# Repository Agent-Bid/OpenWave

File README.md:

# OpenWave

This is an attempt to make an open-source, modern(ish) digital audio player using commonly available parts today with a simple menu-based operating system shell.

## Firmware Build Instructions

This project uses [PlatformIO](https://platformio.org/) for firmware development. The project is being developed with an ESP32 Devkit V1 (esp32dev).

### Prerequisites
* [PlatformIO CLI](https://docs.platformio.org/en/latest/core/index.html)
* Or [PlatformIO IDE - VSCode](https://docs.platformio.org/en/latest/integration/ide/vscode.html)

### Building
1. Navigate to the firmware directory: `cd Firmware/OpenWave_Firmware`
2. Resolve dependencies and build project: `pio run`

### Uploading
1. Connect the ESP32 board via USB and run: `pio run -t upload`
2. To monitor serial from the board: `pio device monitor`

## Hardware Used
All software tested on:
1. ESP32 Devkit V1
2. Adafruit VS1053b Breakout
3. SSD1306 OLED

Custom 4 layer PCB designed in KiCad

## Assembled Board

## Licensing

This is an open-source hardware project. To ensure all aspects of the design are properly protected and freely shareable, the project uses multiple licenses:

* **Software/Firmware:** All code in this repository is licensed under the [MIT License](LICENSE).
* **Hardware/Electronics:** The KiCad schematics and PCB layout files are licensed under the [CERN Open Hardware Licence Version 2 - Strongly Reciprocal (CERN-OHL-S)](LICENSE-HARDWARE.txt).
* **Documentation & Enclosure:** All documentation and the 3D-printable enclosure models (STEP and STL files) are licensed under [Creative Commons Attribution-ShareAlike 4.0 International (CC-BY-SA 4.0)](LICENSE-DOCS.txt).

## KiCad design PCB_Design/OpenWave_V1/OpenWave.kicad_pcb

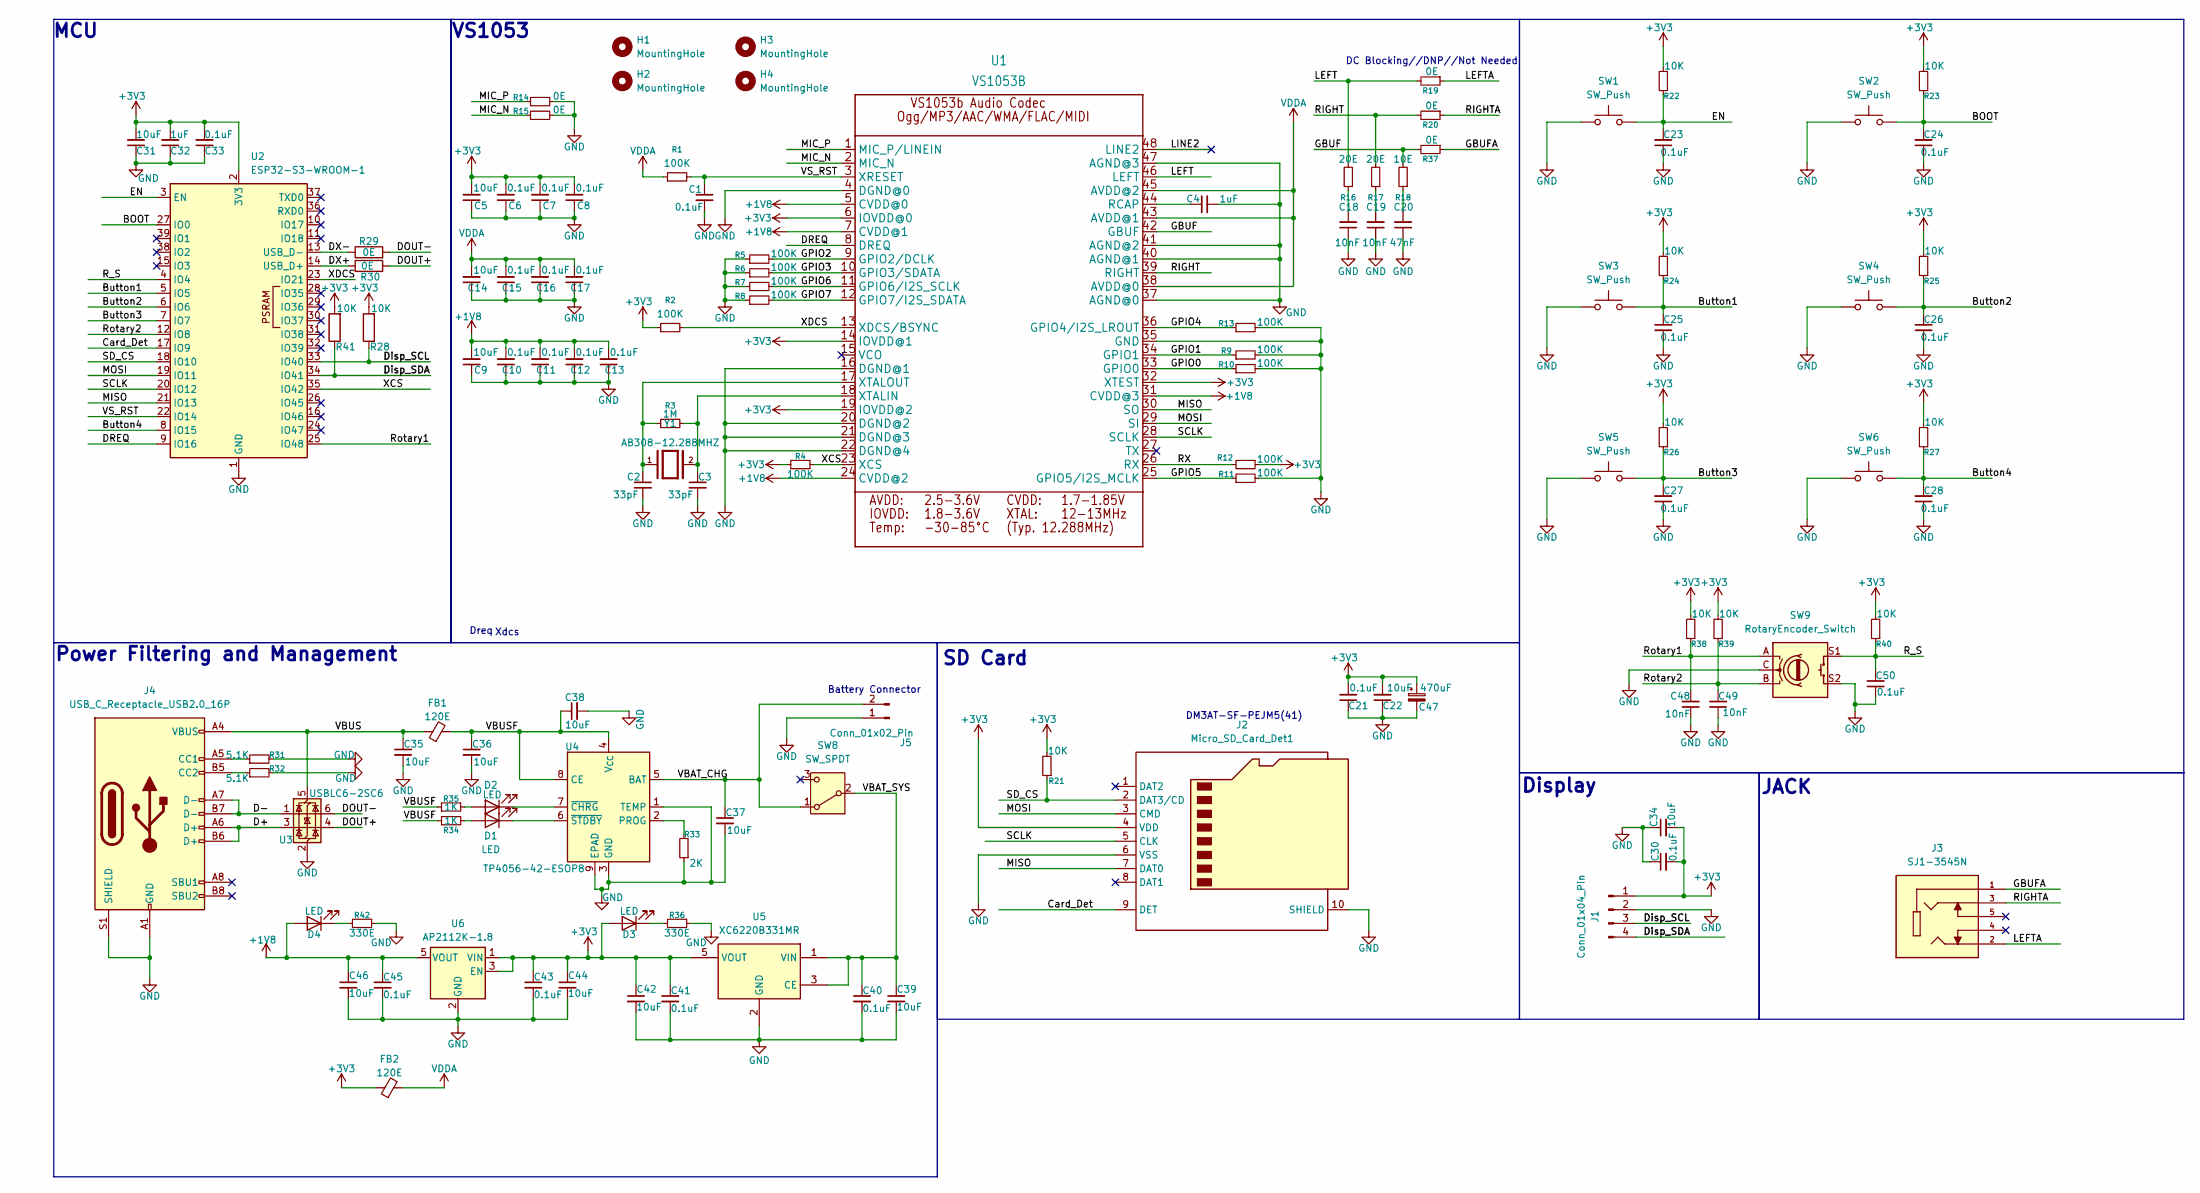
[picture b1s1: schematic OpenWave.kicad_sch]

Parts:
C1, C6, C7, C8, C10, C11, C12, C13, C15, C16, C17, C21, C23, C24, C25, C26, C27, C28, C30, C33, C40, C41, C43, C45, C50: 0.1uF; C_0603_1608Metric
C2, C3: 33pF; C_0603_1608Metric
C4, C32: 1uF; C_0603_1608Metric
C5, C9, C14, C22, C31, C34, C35, C36, C37, C38, C39, C42, C44, C46: 10uF; C_0603_1608Metric
C18, C19, C48, C49: 10nF; C_0603_1608Metric
C20: 47nF; C_0603_1608Metric
C47: 470uF; CP_Radial_D5.0mm_P2.00mm
D1, D2, D3, D4: LED; LED_0603_1608Metric
FB1, FB2: 120E; R_0603_1608Metric
H1, H2, H3, H4: MountingHole; MountingHole_3.2mm_M3
J1: Conn_01x04_Pin; PinHeader_1x04_P2.54mm_Vertical
J2: Micro_SD_Card_Det1; microSD_HC_Hirose_DM3AT-SF-PEJM5
J3: SJ1-3545N; CUI_SJ1-3545N; PARTREV 1.03
J4: USB_C_Receptacle_USB2.0_16P; USB_C_Receptacle_XKB_U262-16XN-4BVC11
J5: Conn_01x02_Pin; JST_EH_B2B-EH-A_1x02_P2.50mm_Vertical
R1, R2, R4, R5, R6, R7, R8, R9, R10, R11, R12, R13: 100K; R_0603_1608Metric
R3: 1M; R_0603_1608Metric
R14, R15, R19, R20, R29, R30, R37: 0E; R_0603_1608Metric
R16, R17: 20E; R_0603_1608Metric
R18: 10E; R_0603_1608Metric
R21, R22, R23, R24, R25, R26, R27, R28, R38, R39, R40, R41: 10K; R_0603_1608Metric
R31, R32: 5.1K; R_0603_1608Metric
R33: 2K; R_0603_1608Metric
R34, R35: 1K; R_0603_1608Metric
R36, R42: 330E; R_0603_1608Metric
SW1, SW2: SW_Push; TS3315A
SW3, SW4, SW5, SW6: SW_Push; SW_Tactile_SPST_Angled_PTS645Vx58-2LFS
SW8: SW_SPDT; SW_Slide_SPDT_Angled_CK_OS102011MA1Q
SW9: RotaryEncoder_Switch; RotaryEncoder_Alps_EC11E-Switch_Vertical_H20mm
U1: VS1053B; LQFP-48_7x7mm_P0.5mm
U2: ESP32-S3-WROOM-1
U3: USBLC6-2SC6; SOT-23-6
U4: TP4056-42-ESOP8; SOIC-8-1EP_3.9x4.9mm_P1.27mm_EP2.41x3.3mm_ThermalVias
U5: XC6220B331MR; SOT-23-5
U6: AP2112K-1.8; SOT-23-5
Y1: AB308-12.288MHZ; XTAL_AB308-12.288MHZ

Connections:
+1V8: C9.2, C10.2, C11.2, C12.2, C13.2, C45.1, C46.1, D4.2 (A), U1.5 (CVDD@0), U1.7 (CVDD@1), U1.24 (CVDD@2), U1.31 (CVDD@3), U6.5 (VOUT)
+3V3: C5.2, C6.2, C7.2, C8.2, C21.2, C22.2, C30.2, C31.2, C32.2, C33.2, C34.2, C41.1, C42.1, C43.1, C44.1, C47.1, D3.2 (A), FB2.1, J1.1, J2.4 (VDD), R2.1, R4.1, R12.1, R21.2, R22.2, R23.2, R24.2, R25.2, R26.2, R27.2, R28.2, R38.2, R39.2, R40.2, R41.2, U1.6 (IOVDD@0), U1.14 (IOVDD@1), U1.19 (IOVDD@2), U1.32 (XTEST), U2.2 (3V3), U5.5 (VOUT), U6.1 (VIN), U6.3 (EN)
/BOOT: C24.2, R23.1, SW2.2, U2.27 (IO0)
/Button1: C25.2, R24.1, SW3.2, U2.5 (IO5)
/Button2: C26.2, R25.1, SW4.2, U2.6 (IO6)
/Button3: C27.2, R26.1, SW5.2, U2.7 (IO7)
/Button4: C28.2, R27.1, SW6.2, U2.8 (IO15)
/Card_Det: J2.9 (DET), U2.17 (IO9)
/D+: J4.A6 (D+), J4.B6 (D+), U3.3 (I/O2)
/D-: J4.A7 (D-), J4.B7 (D-), U3.1 (I/O1)
/DOUT+: R30.2, U3.4 (I/O2)
/DOUT-: R29.2, U3.6 (I/O1)
/DREQ: U1.8 (DREQ), U2.9 (IO16)
/DX+: R30.1, U2.14 (USB_D+)
/DX-: R29.1, U2.13 (USB_D-)
/Disp_SCL: J1.3, R28.1, U2.33 (IO40)
/Disp_SDA: J1.4, R41.1, U2.34 (IO41)
/EN: C23.2, R22.1, SW1.2, U2.3 (EN)
/GBUF: R18.2, R37.2, U1.42 (GBUF)
/GBUFA: J3.1, R37.1
/GPIO0: R10.1, U1.33 (GPIO0)
/GPIO1: R9.1, U1.34 (GPIO1)
/GPIO2: R5.2, U1.9 (GPIO2/DCLK)
/GPIO3: R6.2, U1.10 (GPIO3/SDATA)
/GPIO4: R13.1, U1.36 (GPIO4/I2S_LROUT)
/GPIO5: R11.1, U1.25 (GPIO5/I2S_MCLK)
/GPIO6: R7.2, U1.11 (GPIO6/I2S_SCLK)
/GPIO7: R8.2, U1.12 (GPIO7/I2S_SDATA)
/LEFT: R16.2, R19.2, U1.46 (LEFT)
/LEFTA: J3.2, R19.1
/LINE2: U1.48 (LINE2)
/MIC_N: R15.1, U1.2 (MIC_N)
/MIC_P: R14.1, U1.1 (MIC_P/LINEIN)
/MISO: J2.7 (DAT0), U1.30 (SO), U2.21 (IO13)
/MOSI: J2.3 (CMD), U1.29 (SI), U2.19 (IO11)
/RIGHT: R17.2, R20.2, U1.39 (RIGHT)
/RIGHTA: J3.3, R20.1
/RX: R12.2, U1.26 (RX)
/R_S: C50.2, R40.1, SW9.S1, U2.4 (IO4)
/Rotary1: C48.2, R38.1, SW9.A, U2.25 (IO48)
/Rotary2: C49.2, R39.1, SW9.B, U2.12 (IO8)
/SCLK: J2.5 (CLK), U1.28 (SCLK), U2.20 (IO12)
/SD_CS: J2.2 (DAT3/CD), R21.1, U2.18 (IO10)
/VBAT_CHG: C37.1, J5.2, SW8.1 (A), U4.5 (BAT)
/VBAT_SYS: C39.1, C40.1, SW8.2 (B), U5.1 (VIN), U5.3 (CE)
/VBUS: C35.1, FB1.1, J4.A4 (VBUS), J4.A9 (VBUS), J4.B4 (VBUS), J4.B9 (VBUS), U3.5 (VBUS)
/VBUSF: C36.1, C38.1, FB1.2, R34.1, R35.1, U4.4 (V_{CC}), U4.8 (CE)
/VS_RST: C1.1, R1.2, U1.3 (XRESET), U2.22 (IO14)
/XCS: R4.2, U1.23 (XCS), U2.35 (IO42)
/XDCS: R2.2, U1.13 (XDCS/BSYNC), U2.23 (IO21)
GND: C1.2, C2.2, C3.2, C4.2, C5.1, C6.1, C7.1, C8.1, C9.1, C10.1, C11.1, C12.1, C13.1, C14.1, C15.1, C16.1, C17.1, C18.1, C19.1, C20.1, C21.1, C22.1, C23.1, C24.1, C25.1, C26.1, C27.1, C28.1, C30.1, C31.1, C32.1, C33.1, C34.1, C35.2, C36.2, C37.2, C38.2, C39.2, C40.2, C41.2, C42.2, C43.2, C44.2, C45.2, C46.2, C47.2, C48.1, C49.1, C50.1, J1.2, J2.6 (VSS), J2.10 (SHIELD), J4.A1 (GND), J4.A12 (GND), J4.B1 (GND), J4.B12 (GND), J4.S1 (SHIELD), J5.1, R5.1, R6.1, R7.1, R8.1, R9.2, R10.2, R11.2, R13.2, R14.2, R15.2, R31.2, R32.2, R33.1, R36.1, R42.1, SW1.1, SW2.1, SW3.1, SW4.1, SW5.1, SW6.1, SW9.C, SW9.S2, U1.4 (DGND@0), U1.16 (DGND@1), U1.20 (DGND@2), U1.21 (DGND@3), U1.22 (DGND@4), U1.35 (GND), U1.37 (AGND@0), U1.40 (AGND@1), U1.41 (AGND@2), U1.47 (AGND@3), U2.1 (GND), U2.40 (GND), U2.41 (GND), U3.2 (GND), U4.1 (TEMP), U4.3 (GND), U4.9 (EPAD), U5.2 (GND), U6.2 (GND)
unnamed: C18.2, R16.1
unnamed: C19.2, R17.1
unnamed: C20.2, R18.1
unnamed: D1.2 (A), R34.2
unnamed: D1.1 (K), U4.6 (~STDBY)
unnamed: D2.2 (A), R35.2
unnamed: D2.1 (K), U4.7 (~CHRG)
unnamed: D3.1 (K), R36.2
unnamed: D4.1 (K), R42.2
unnamed: J4.A5 (CC1), R31.1
unnamed: J4.B5 (CC2), R32.1
unnamed: C4.1, U1.44 (RCAP)
unnamed: C3.1, R3.2, U1.18 (XTALIN), Y1.2
unnamed: C2.1, R3.1, U1.17 (XTALOUT), Y1.1
unnamed: R33.2, U4.2 (PROG)
VDDA: C14.2, C15.2, C16.2, C17.2, FB2.2, R1.1, U1.38 (AVDD@0), U1.43 (AVDD@1), U1.45 (AVDD@2)

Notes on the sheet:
DM3AT-SF-PEJM5(41)
Display
Battery Connector
Dreq
MCU
SD Card
DC Blocking//DNP//Not Needed
Xdcs
Power Filtering and Management
VS1053
JACK

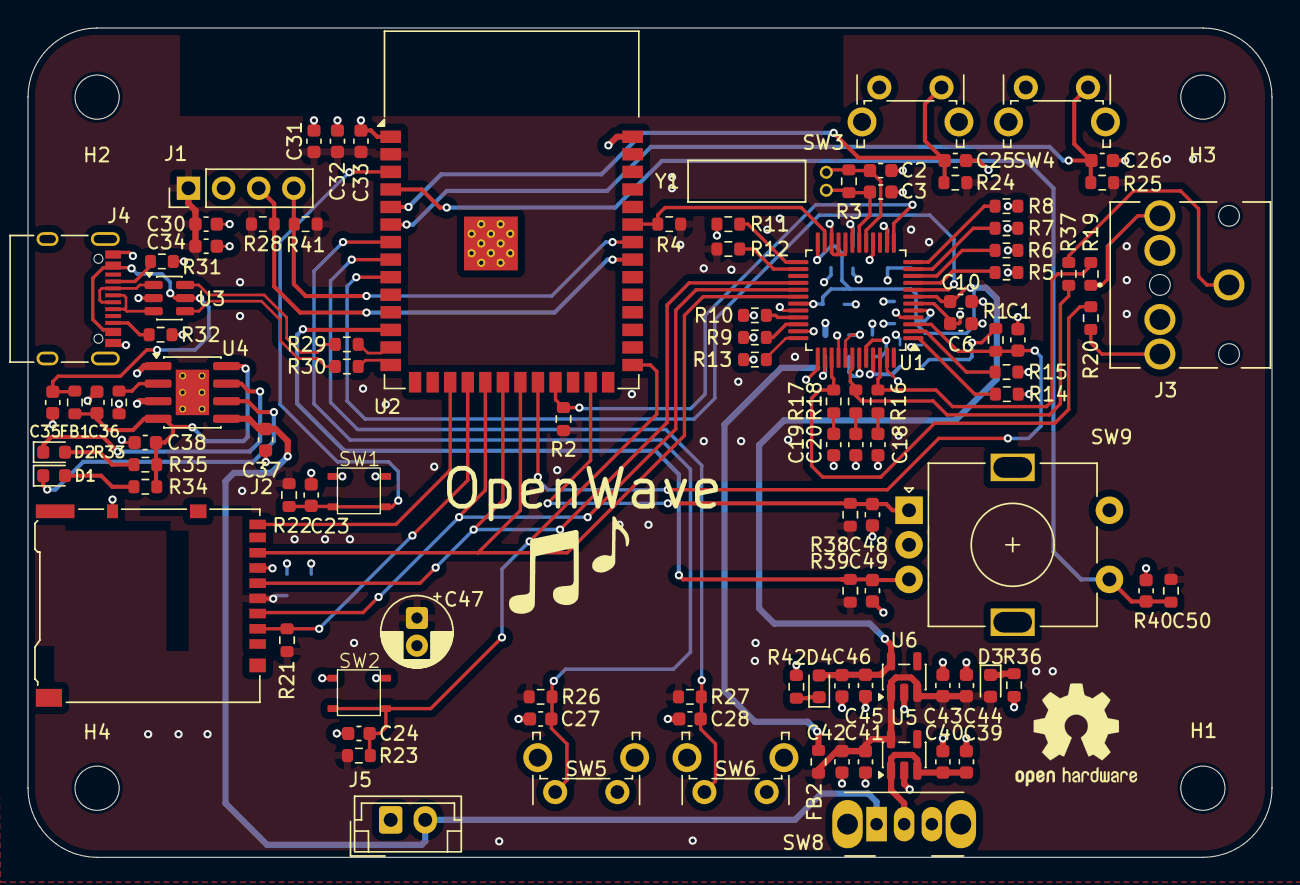
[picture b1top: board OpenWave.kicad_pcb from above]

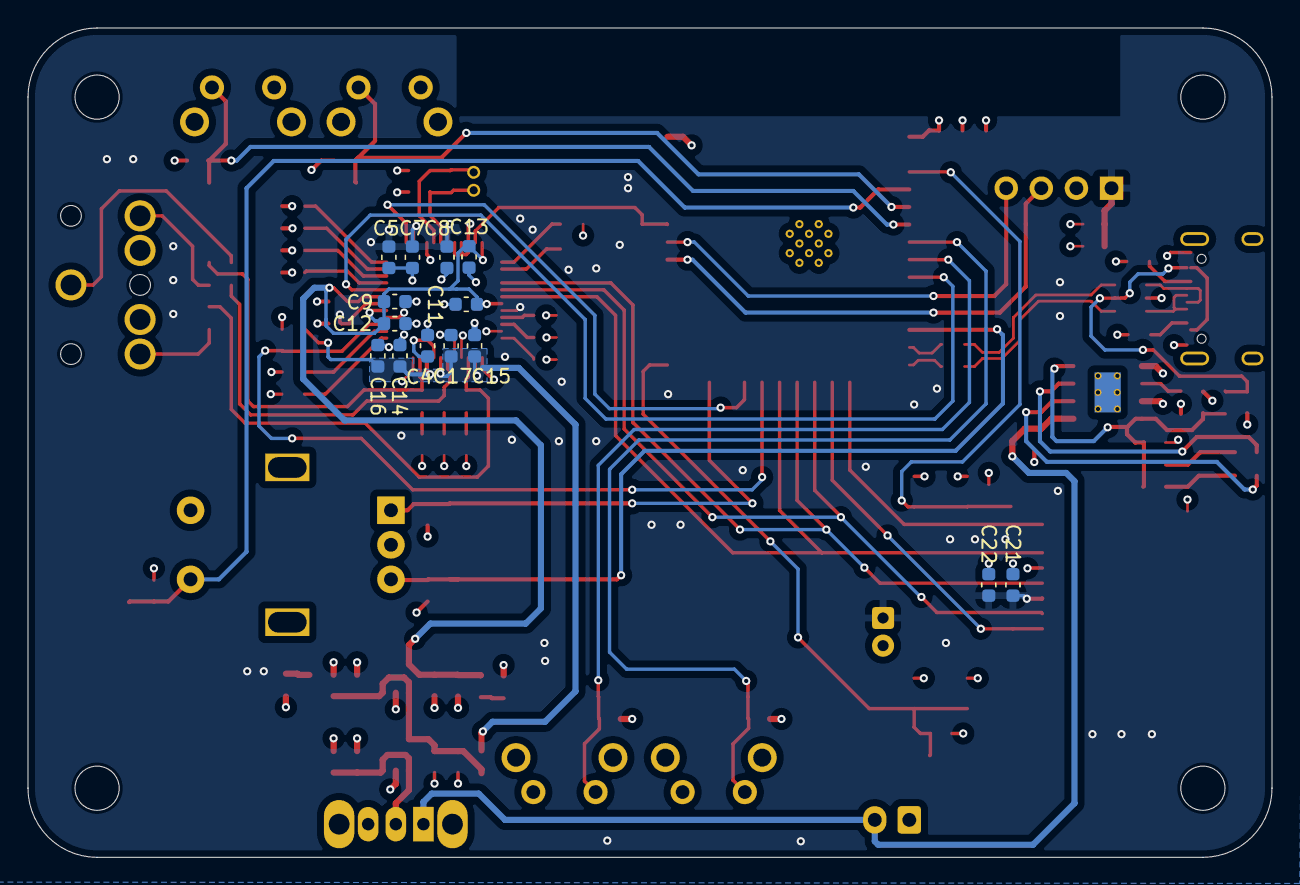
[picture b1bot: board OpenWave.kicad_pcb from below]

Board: 4 copper layers, 90.0 x 60.0 mm, 121 parts (14 on the bottom side), 66 nets.

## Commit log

2025-12-05 Initial Commit , Basic Display Firmware
2025-12-05 Implemented menu scrolling and added settings, updated state machine.
2025-12-06 Added non functional settings menu with WiFi and BT.
2025-12-06 Switched to RAM buffered UI for track selection
2025-12-06 Added WiFi functionality for NTP time using FreeRTOS
2025-12-08 Changed all blocking delays to non blocking delays + General Optimization.
2025-12-10 Implemented scrollable tracks menu and improved memory allocation on track selection menu
2025-12-12 Added the README
2025-12-16 Changed song selection menu from hardcoded text to dynamic file reading system, made minor refinements.
2025-12-18 Added audio functionality using the Adafruit VS1053 Codec, implemented playlist looping.
2025-12-20 Minor bug fixes with the song selection and looping logic. Tested with Codec
2025-12-20 Made tweaks to the state machine, added song switching in pause and track switching in the song state.
2025-12-22 Added a functional audio equalizer for the bass and treble amplitudes, updated minor state machine logic.
2025-12-27 Initialized PCB Design and added cut off frequency options to the equalizer.
2025-12-27 Implementing bitmap based UI.
2026-01-01 Updated schematics with a headphone amp. WIP
2026-01-05 Added basic volume change functionality in settings.
2026-01-06 Basic power management code(sleep when inactive)
2026-01-10 Refactored power manager, changed headphone amp to PAM8908 in shcematics.
2026-02-01 Basic 3D design of the case, updated pcb dimensions.
2026-02-09 Minor Updates to the Schematics, removed headphone Amp IC
2026-02-09 Deleted old case designs
2026-02-18 Updated Routing for PCB
2026-02-18 Updated PCB routing
2026-02-21 Completed PCB Design, Updated Licences and Readme.
2026-02-24 Added power indicators and silkscreen
2026-02-25 Minor tracing updates
2026-03-09 Updated BOM, Changed ESP pin defs.
2026-03-09 Updated BOM
2026-03-30 Allow tracking of Screenshots/ and add project screenshots to README
2026-03-30 Correct building instructions in README.md
